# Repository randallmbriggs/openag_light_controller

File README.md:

# openag_light_controller
PCB for controlling a multi-channel light panel

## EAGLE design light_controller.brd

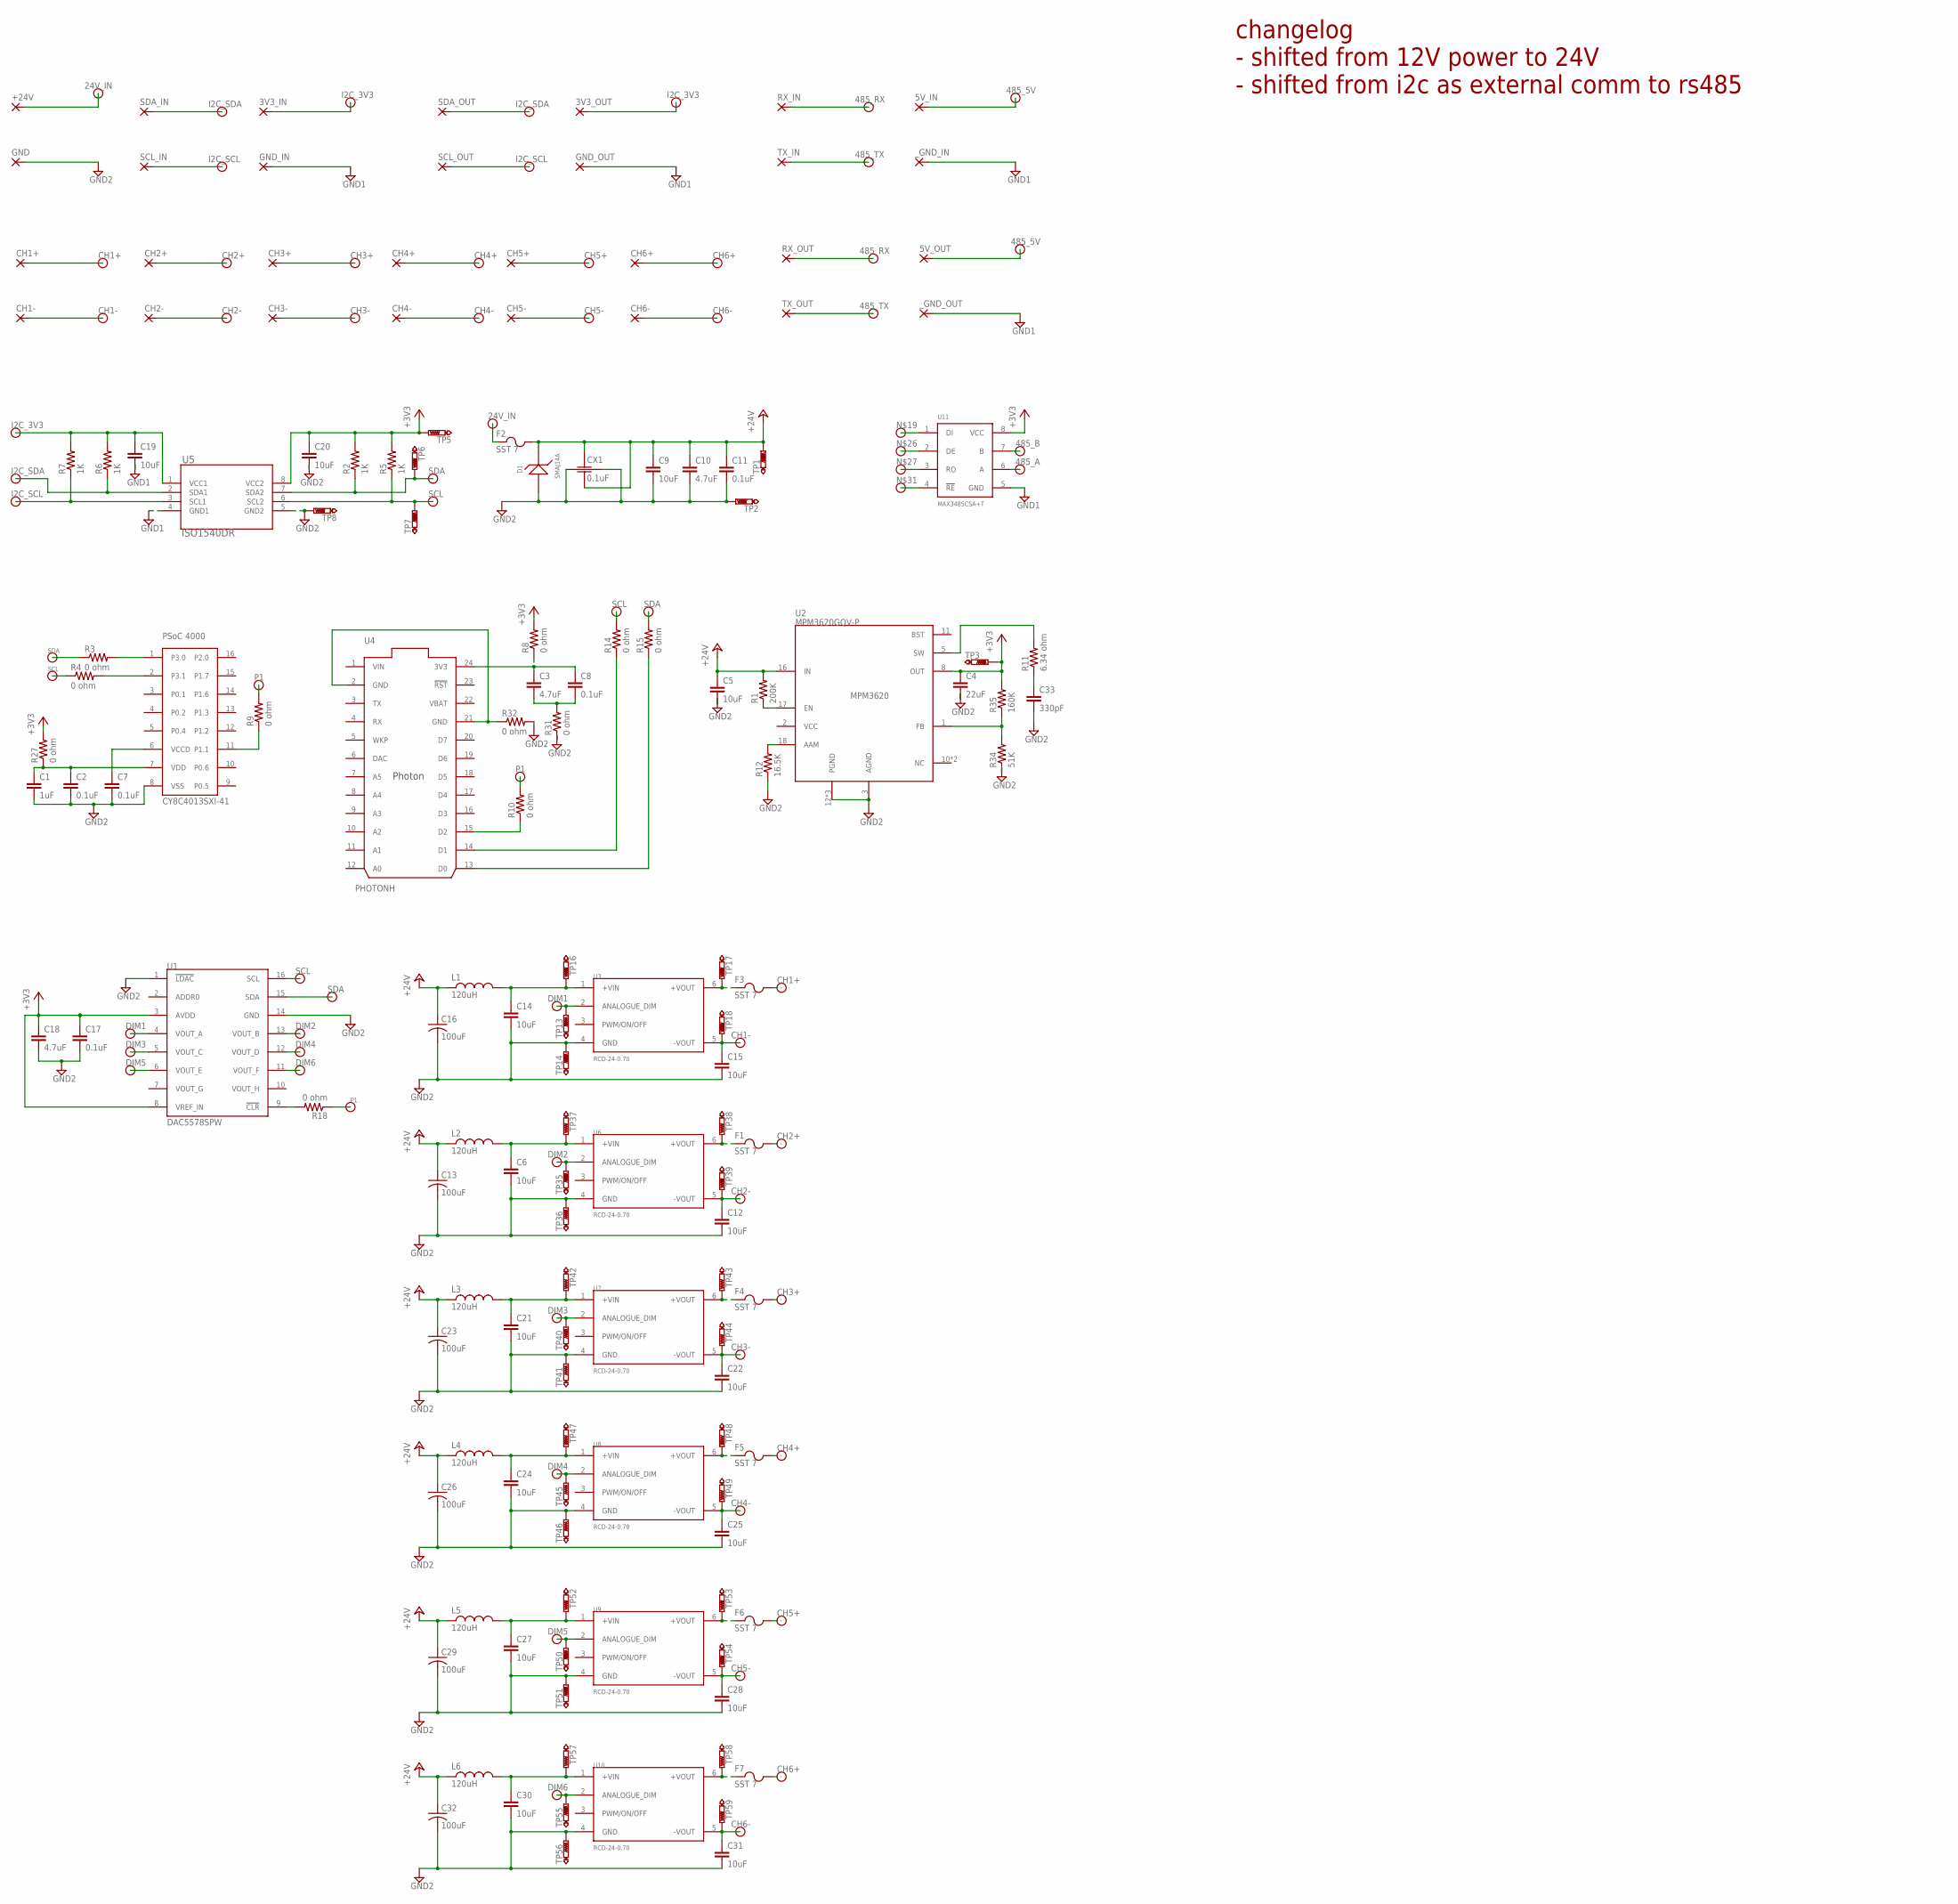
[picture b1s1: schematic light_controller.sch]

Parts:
3V3_IN, 3V3_OUT, 5V_IN, 5V_OUT: 3,17/1,3
+24V: 3,17/1,3
C1: 1uF; C1206
C2, C7, C8, C11, C17: 0.1uF; C1206C
C3, C10, C18: 4.7uF; CAP_C1206
C4: 22uF; C1206
C5, C6, C9, C12, C14, C15, C19, C20, C21, C22, C24, C25, C27, C28, C30, C31: 10uF; C1206
C13, C16, C23, C26, C29, C32: 100uF; EEE-1HA101UP
C33: 330pF; C1206
CH1+, CH1-, CH2+, CH2-, CH3+, CH3-, CH4+, CH4-, CH5+, CH5-, CH6+, CH6-: 3,17/1,3
CX1: 0.1uF; CX1206
D1: SMAJ14A; DO-214AC
F1, F2, F3, F4, F5, F6, F7: SST 7; SS
GND: 3,17/1,3
GND_IN: 3,17/1,3
GND_OUT: 3,17/1,3
L1, L2, L3, L4, L5, L6: 120uH; 74404064121
R1: 200K; RC0603N
R2, R5, R6, R7: 1K; RC0603N
R3, R4, R8, R9, R10, R14, R15, R18, R27, R31, R32: 0 ohm; RC0603N
R11: 6.34 ohm; R0805
R12: 16.5K; RC0603N
R34: 51K; RC0603N
R35: 160K; RC0603N
RX_IN: 3,17/1,3
RX_OUT: 3,17/1,3
SCL_IN: 3,17/1,3
SCL_OUT: 3,17/1,3
SDA_IN: 3,17/1,3
SDA_OUT: 3,17/1,3
TP1, TP2, TP3, TP5, TP6, TP7, TP8, TP13, TP14, TP16, TP17, TP18, TP35, TP36, TP37, TP38, TP39, TP40, TP41, TP42, TP43, TP44, TP45, TP46, TP47, TP48, TP49, TP50, TP51, TP52, TP53, TP54, TP55, TP56, TP57, TP58, TP59: PTR1B2,54; B2,54
TX_IN: 3,17/1,3
TX_OUT: 3,17/1,3
U1: DAC5578SPW; TSSOP16
U2: MPM3620GQV-P; 20-POWERLFQFN-MODULE
U3, U6, U7, U8, U9, U10: RCD-24-0.70; RCD-24-PINNED
U4: PHOTONH; PHOTON
U5: ISO1540DR; D8
U11: MAX3485CSA+T; SOIC8
U$2: CY8C4013SXI-41; SOIC16
_GND_IN: 3,17/1,3
_GND_OUT: 3,17/1,3

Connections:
24V_IN: +24V.1, F2.1
485_5V: 5V_IN.1, 5V_OUT.1
485_A: U11.6 (A)
485_B: U11.7 (B)
485_RX: RX_IN.1, RX_OUT.1
485_TX: TX_IN.1, TX_OUT.1
+3V3: C4.1, C17.1, C18.1, C20.1, R2.2, R5.2, R8.2, R27.2, R35.2, TP3.TP, TP5.TP, U1.3 (AVDD), U1.8 (VREF_IN), U2.8 (OUT), U5.8 (VCC2), U11.8 (VCC)
+24V: C5.1, C9.1, C10.1, C11.1, C13.+ (1(+)), C16.+ (1(+)), C23.+ (1(+)), C26.+ (1(+)), C29.+ (1(+)), C32.+ (1(+)), CX1.1 (11), CX1.2 (22), D1.C, F2.2, L1.1, L2.1, L3.1, L4.1, L5.1, L6.1, R1.2, TP1.TP, U2.16 (IN)
CH1+: CH1+.1, F3.2
CH1-: C15.1, CH1-.1, TP18.TP, U3.5 (-VOUT)
CH2+: CH2+.1, F1.2
CH2-: C12.1, CH2-.1, TP39.TP, U6.5 (-VOUT)
CH3+: CH3+.1, F4.2
CH3-: C22.1, CH3-.1, TP44.TP, U7.5 (-VOUT)
CH4+: CH4+.1, F5.2
CH4-: C25.1, CH4-.1, TP49.TP, U8.5 (-VOUT)
CH5+: CH5+.1, F6.2
CH5-: C28.1, CH5-.1, TP54.TP, U9.5 (-VOUT)
CH6+: CH6+.1, F7.2
CH6-: C31.1, CH6-.1, TP59.TP, U10.5 (-VOUT)
DIM1: TP13.TP, U1.4 (VOUT_A), U3.2 (ANALOGUE_DIM)
DIM2: TP35.TP, U1.13 (VOUT_B), U6.2 (ANALOGUE_DIM)
DIM3: TP40.TP, U1.5 (VOUT_C), U7.2 (ANALOGUE_DIM)
DIM4: TP45.TP, U1.12 (VOUT_D), U8.2 (ANALOGUE_DIM)
DIM5: TP50.TP, U1.6 (VOUT_E), U9.2 (ANALOGUE_DIM)
DIM6: TP55.TP, U1.11 (VOUT_F), U10.2 (ANALOGUE_DIM)
GND1: C19.2, GND_IN.1, GND_OUT.1, U5.4 (GND1), U11.5 (GND), _GND_IN.1, _GND_OUT.1
GND2: C1.2, C2.2, C4.2, C5.2, C6.2, C7.2, C9.2, C10.2, C11.2, C12.2, C13.- (2(-)), C14.2, C15.2, C16.- (2(-)), C17.2, C18.2, C20.2, C21.2, C22.2, C23.- (2(-)), C24.2, C25.2, C26.- (2(-)), C27.2, C28.2, C29.- (2(-)), C30.2, C31.2, C32.- (2(-)), C33.2, CX1.3 (33), CX1.4 (44), D1.A, GND.1, R12.1, R31.1, R32.2, R34.1, TP2.TP, TP8.TP, TP14.TP, TP36.TP, TP41.TP, TP46.TP, TP51.TP, TP56.TP, U1.1 (!LDAC!), U1.14 (GND), U2.3 (AGND), U2.12 (PGND), U2.13 (PGND), U2.14 (PGND), U3.4 (GND), U5.5 (GND2), U6.4 (GND), U7.4 (GND), U8.4 (GND), U9.4 (GND), U10.4 (GND), U$2.8 (VSS)
I2C_3V3: 3V3_IN.1, 3V3_OUT.1, C19.1, R6.2, R7.2, U5.1 (VCC1)
I2C_SCL: R7.1, SCL_IN.1, SCL_OUT.1, U5.3 (SCL1)
I2C_SDA: R6.1, SDA_IN.1, SDA_OUT.1, U5.2 (SDA1)
unnamed: R3.2, U$2.1 (P3.0)
unnamed: R4.2, U$2.2 (P3.1)
unnamed: C14.1, L1.2, TP16.TP, U3.1 (+VIN)
unnamed: R9.1, U$2.11 (P1.1)
unnamed: F3.1, TP17.TP, U3.6 (+VOUT)
unnamed: C6.1, L2.2, TP37.TP, U6.1 (+VIN)
unnamed: R10.1, U4.15 (D2)
unnamed: R18.2, U1.9 (!CLR!)
unnamed: F1.1, TP38.TP, U6.6 (+VOUT)
unnamed: C21.1, L3.2, TP42.TP, U7.1 (+VIN)
unnamed: F4.1, TP43.TP, U7.6 (+VOUT)
unnamed: C24.1, L4.2, TP47.TP, U8.1 (+VIN)
unnamed: F5.1, TP48.TP, U8.6 (+VOUT)
unnamed: C27.1, L5.2, TP52.TP, U9.1 (+VIN)
unnamed: R11.2, U2.5 (SW)
unnamed: C1.1, C2.1, R27.1, U$2.7 (VDD)
unnamed: C33.1, R11.1
unnamed: R12.2, U2.18 (AAM)
unnamed: C3.2, C8.2, R31.2
unnamed: F6.1, TP53.TP, U9.6 (+VOUT)
unnamed: R14.1, U4.14 (D1)
unnamed: C3.1, C8.1, R8.1, U4.24 (3V3)
unnamed: C30.1, L6.2, TP57.TP, U10.1 (+VIN)
unnamed: F7.1, TP58.TP, U10.6 (+VOUT)
unnamed: R15.1, U4.13 (D0)
unnamed: C7.1, U$2.6 (VCCD)
unnamed: R32.1, U4.2 (GND), U4.21 (GND)
unnamed: R1.1, U2.17 (EN)
unnamed: R34.2, R35.1, U2.1 (FB)
P1: R9.2, R10.2, R18.1
SCL: R4.1, R5.1, R14.2, TP7.TP, U1.16 (SCL), U5.6 (SCL2)
SDA: R2.1, R3.1, R15.2, TP6.TP, U1.15 (SDA), U5.7 (SDA2)
VBAT: U4.22 (VBAT)
VIN: U4.1 (VIN)

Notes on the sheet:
changelog - shifted from 12V power to 24V - shifted from i2c as external comm to rs485

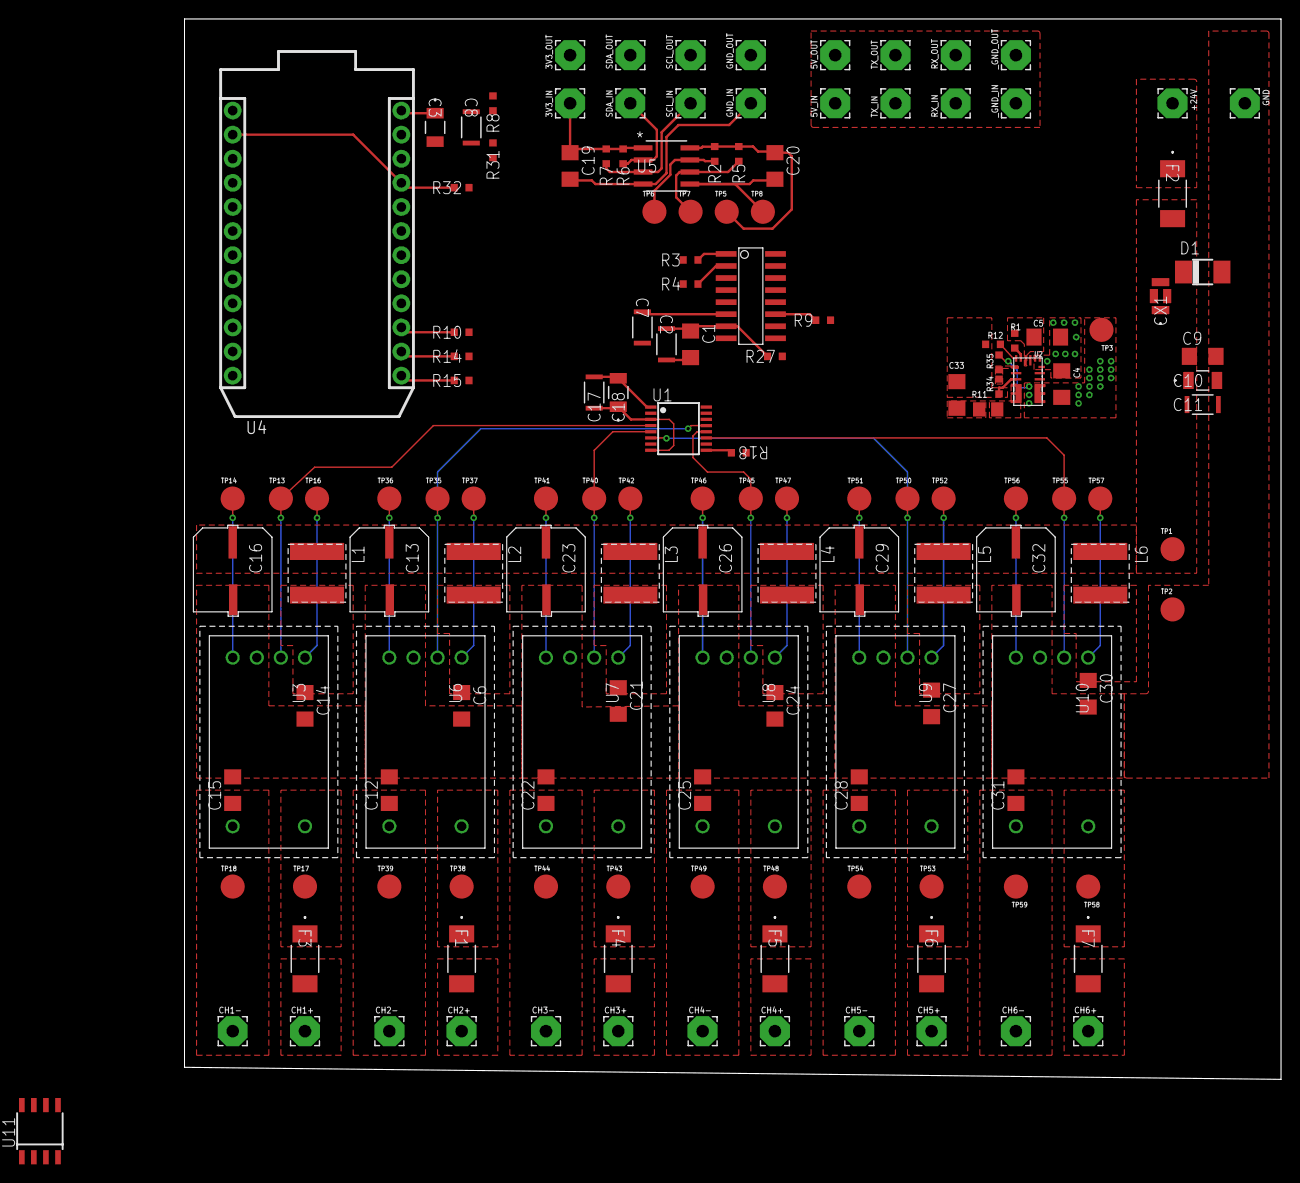
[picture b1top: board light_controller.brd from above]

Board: 2 copper layers, 115.6 x 111.8 mm, 147 parts (0 on the bottom side), 61 nets.

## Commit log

2017-10-12 added dac and const current regulator
2017-10-17 updated all elements in schematic to be from openag_eagle_library repo
2017-10-18 calculated power consuption, cleaned up mcu 0ohnm resistors
2017-10-18 added 3v3 syncronous regulator module
2017-10-23 added x2y cap for 24v conditioning and testpoints for self-contined module testing
2017-10-25 routed current regulators and 3.3v sync regulators, added rs485 to ttl transceiver
